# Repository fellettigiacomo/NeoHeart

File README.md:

# NeoHeart - Revision 2.2🎉
Hardware and Software design for an Open Source ATtiny816-based heart shaped PCB with Addressable LEDs.
<br><br>⚠️ **Warning**: Unfortunately, this release is not yet ready for production. There are still issues with the CR2032 battery not providing enough power, causing glitches and freezes in the LEDs. I'm currently working on a fix. ⚠️
<br><br>
## Project sponsor: PCBWay
Thanks to [PCBWay](https://www.pcbway.com/) for sponsoring this open-source project. Check out the sponsorship section below to learn more about their support.

## Features

- **Microcontroller**: ATtiny816
- **LEDs**: 25 SK6805-MINIJ Addressable RGB LEDs
- **Power**: 3V CR2032 battery
- **Programming**: UPDI programming interface
- **Software**: Built using Adafruit's Neopixel library, featuring 10 built-in animations and efficient power management
- **Additional Features**:
  - Low current consumption design
  - Integrated MOSFET for powering down LEDs to save power
  - Additional digital/analog exposed GPIO to hack your NeoHeart in unexpected ways
  
## 2.2 Upgrades

- **Efficient power design**: the TPS61240 boost converter has been fully redesigned—now controlled by the MCU via the Enable pin (no more external MOSFET). Improved input stability with additional capacitors, removed feedback resistors for better overall efficiency.
- **Extended Battery Life**: ultra-low 0.14 µA quiescent current enables over 10 years of idle operation and supports 1000+ button presses on a single CR2032 cell.
- **Enhanced ATiny816 Stability**: added decoupling capacitors to ensure reliable and noise-free microcontroller performance.
- **Upgraded Battery Holder**: replaced the CR2032 holder with a more robust and durable version to prevent mechanical failure.
- **Improved Grounding**: added a dedicated ground plane for better signal integrity and reduced noise.
    
## Getting Started

To get started with NeoHeart, follow these steps:
1. **Assembly**: 
   - If you didn't assemble the back using economic PCBA (which I recommend), solder the [battery holder](https://aliexpress.com/item/1005005506756152.html).
2. **Powering the Board**:
   - Insert a CR2032 battery into the battery holder, ensuring the positive side of the battery matches the positive marking on the board. Alternatively, you can also power the board with the 5V and GND headers
3. **Installing Software**:
   - Install the Legacy version of the [Arduino IDE](https://www.arduino.cc/en/software) (otherwise you will get the *a programmer is required to upload* error) or [PlatformIO](https://platformio.org/platformio-ide)
   - Install the Adafruit NeoPixel library.
4. **Connecting the Programmer**:
   - Connect your UPDI programmer to the UPDI header on your NeoHeart board. If using an Arduino or any other serial adapter that supports JTAG, follow the instructions provided [here](https://github.com/ElTangas/jtag2updi).
5. **Uploading the Firmware**:
   - Open the firmware sketch provided in the repository.
   - Select the correct board and port in your IDE of choice.
   - Click on the upload button to flash your NeoHeart.
6. **Enjoy**:
   - Once programmed, your NeoHeart will be ready to go. Just hit the button and watch those LEDs light up!

## Manufacturing
Without including taxes, shipping and with current parts pricing 5 assembled boards (front only, having to solder the battery holder yourself) will cost around 52 USD dollars, so around 10 bucks a board.
<br><br>You can find all the files for production in the *releases* tab of this repository.
<br>All parts should available and ready to order, otherwise, feel free to send me a pull request.

## Contributing
Any contribution aimed to improving the software or the hardware of NeoHeart are very welcomed. 
Please feel free to fork this repo, make changes, and submit pull requests.

## PCBWay
I've been able to prototype the latest NeoHeart Release thanks to PCBWay that reached out to sponsor this project.
<br> You can see a photo of the boards that PCBWay sent me down here, you can also watch my unboxing video [here](https://youtu.be/b7MC2HfKiS8)
### Why PCBWay?
- **Quality and Reliability**: PCBWay's PCBs meet the highest standards of quality and reliability, they are also capable of meeting the technical demands of any project, from simple projects like mine to very complicated projects.
- **Customization and Flexibility**: They offer extensive customization options, allowing board designers to tailor their PCBs precisely to their project's needs.
- **Community Support**: PCBWay is a strong supporter of open-source projects, offering sponsorships and discounts to help bring these community-beneficial projects to life. Their commitment to the open-source community makes them a particularly good match for community-driven initiatives.
- **Rapid Prototyping**: Time is very important in project development, and PCBWay’s rapid prototyping service allows for quick turnarounds without sacrificing quality.

### My Experience with PCBWay
It's been fantastic: our collaboration not only consisted in receiving high-quality PCBs (with PCBA), experiencing a seamless process facilitated by their expert team, from selecting the right components to checking for errors. 
<br>I've also received photos of the assembled boards before shipping to ensure everything was perfect!.
<br><br>Despite different time zones, the response time from their support team was impressive, which I found incredibly helpful.
<br><br>As I said before, I think it's fantastic that big companies like PCBWay are committed to the open-source community, helping students worldwide bring their projects to life. <b> Thanks again PCBWay!! </b>

## License
CERN Open Hardware License - Strongly Reciprocal (CERN-OHL-S)

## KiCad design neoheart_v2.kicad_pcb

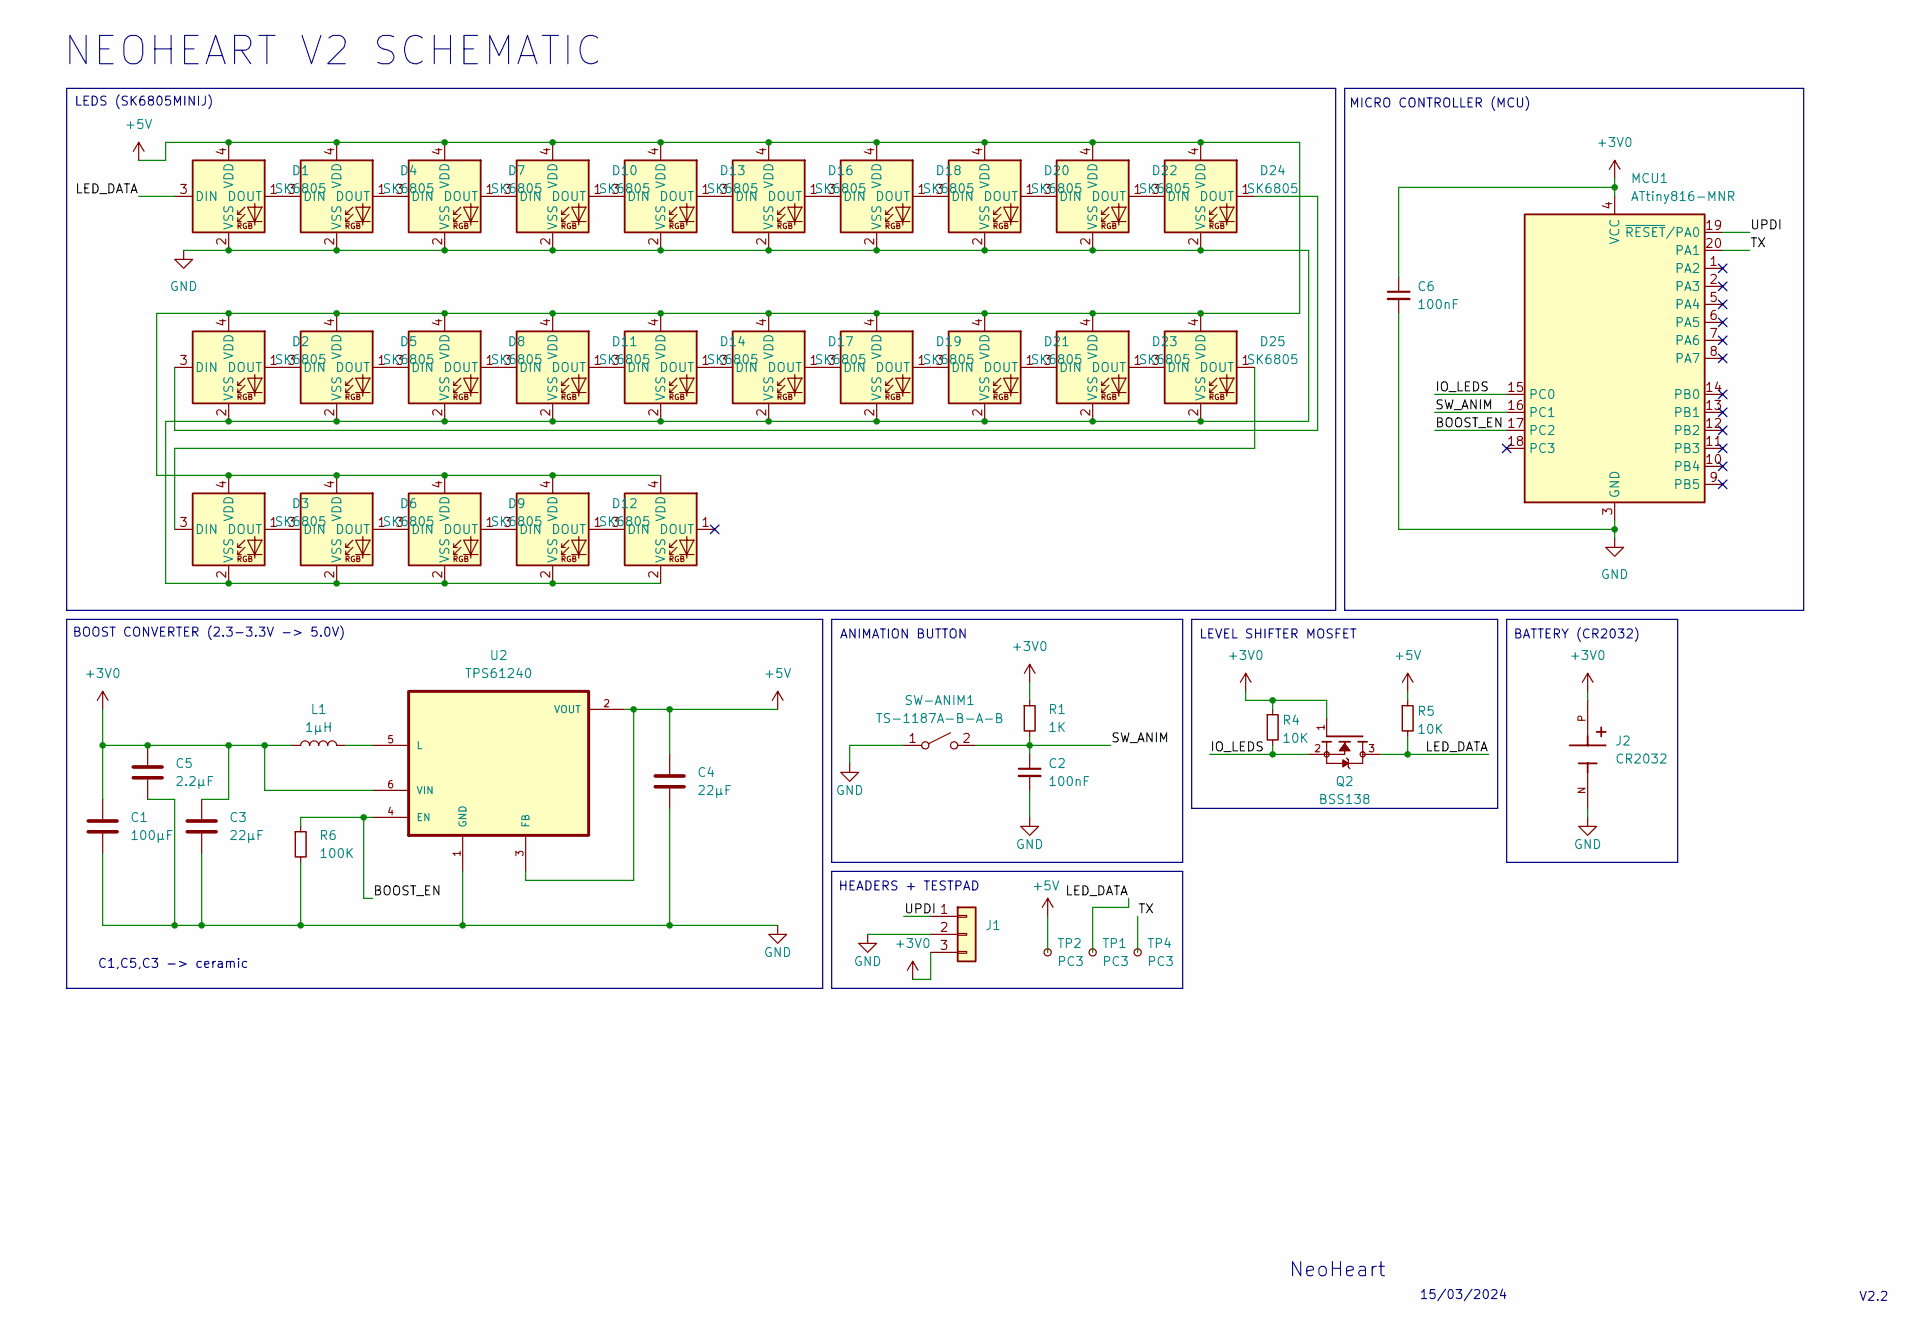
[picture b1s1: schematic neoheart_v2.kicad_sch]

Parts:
C1: 100µF; C_1210_3225Metric_Pad1.33x2.70mm_HandSolder
C2: 100nF; C_0402_1005Metric_Pad0.74x0.62mm_HandSolder
C3: 22μF; C_0805_2012Metric_Pad1.18x1.45mm_HandSolder
C4: 22μF; C_0603_1608Metric_Pad1.08x0.95mm_HandSolder
C5: 2.2µF; C_0805_2012Metric_Pad1.18x1.45mm_HandSolder
C6: 100nF; C_0603_1608Metric
D1, D2, D3, D4, D5, D6, D7, D8, D9, D10, D11, D12, D13, D14, D15, D16, D17, D18, D19, D20, D21, D22, D23, D24, D25: SK6805; LED_SK6805_PLCC4_2.4x2.7mm_P1.3mm
J1: Conn_01x03; PinHeader_1x03_P2.54mm_Vertical
J2: CR2032; HARWIN_S8421-45R; PARTREV 7
L1: 1μH; L_0805_2012Metric_Pad1.05x1.20mm_HandSolder
MCU1: ATtiny816-MNR; VQFN-20-1EP_3x3mm_P0.4mm_EP1.7x1.7mm
Q2: BSS138; SOT95P237X112-3N; PARTREV April 24, 2014
R1: 1K; R_0402_1005Metric_Pad0.72x0.64mm_HandSolder
R4, R5: 10K; R_0402_1005Metric_Pad0.72x0.64mm_HandSolder
R6: 100K; R_0805_2012Metric_Pad1.20x1.40mm_HandSolder
SW-ANIM1: TS-1187A-B-A-B; SW_Push_1P1T_XKB_TS-1187A
TP1, TP2, TP4: PC3; TestPoint_Pad_D1.5mm
U2: TPS61240; SON65P200X200X80-7N

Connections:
+3V0: C1.1, C3.1, C5.1, C6.1, J1.3, J2.P, L1.1, MCU1.4 (VCC), Q2.1, R1.1, R4.1, U2.6 (VIN)
+5V: C4.1, D1.4 (VDD), D2.4 (VDD), D3.4 (VDD), D4.4 (VDD), D5.4 (VDD), D6.4 (VDD), D7.4 (VDD), D8.4 (VDD), D9.4 (VDD), D10.4 (VDD), D11.4 (VDD), D12.4 (VDD), D13.4 (VDD), D14.4 (VDD), D15.4 (VDD), D16.4 (VDD), D17.4 (VDD), D18.4 (VDD), D19.4 (VDD), D20.4 (VDD), D21.4 (VDD), D22.4 (VDD), D23.4 (VDD), D24.4 (VDD), D25.4 (VDD), R5.1, TP2.1, U2.2 (VOUT), U2.3 (FB)
/BOOST_EN: MCU1.17 (PC2), R6.1, U2.4 (EN)
/IO_LEDS: MCU1.15 (PC0), Q2.2, R4.2
/LED_DATA: D1.3 (DIN), Q2.3, R5.2, TP1.1
/SW_ANIM: C2.1, MCU1.16 (PC1), R1.2, SW-ANIM1.2 (B)
/TX: MCU1.20 (PA1), TP4.1
/UPDI: J1.1, MCU1.19 (~RESET/PA0)
GND: C1.2, C2.2, C3.2, C4.2, C5.2, C6.2, D1.2 (VSS), D2.2 (VSS), D3.2 (VSS), D4.2 (VSS), D5.2 (VSS), D6.2 (VSS), D7.2 (VSS), D8.2 (VSS), D9.2 (VSS), D10.2 (VSS), D11.2 (VSS), D12.2 (VSS), D13.2 (VSS), D14.2 (VSS), D15.2 (VSS), D16.2 (VSS), D17.2 (VSS), D18.2 (VSS), D19.2 (VSS), D20.2 (VSS), D21.2 (VSS), D22.2 (VSS), D23.2 (VSS), D24.2 (VSS), D25.2 (VSS), J1.2, J2.N, MCU1.3 (GND), MCU1.21 (GND), R6.2, SW-ANIM1.1 (A), U2.1 (GND)
unnamed: D1.1 (DOUT), D4.3 (DIN)
unnamed: D2.3 (DIN), D24.1 (DOUT)
unnamed: D2.1 (DOUT), D5.3 (DIN)
unnamed: D3.1 (DOUT), D6.3 (DIN)
unnamed: D4.1 (DOUT), D7.3 (DIN)
unnamed: D5.1 (DOUT), D8.3 (DIN)
unnamed: D6.1 (DOUT), D9.3 (DIN)
unnamed: D7.1 (DOUT), D10.3 (DIN)
unnamed: D10.1 (DOUT), D13.3 (DIN)
unnamed: D8.1 (DOUT), D11.3 (DIN)
unnamed: D11.1 (DOUT), D14.3 (DIN)
unnamed: D9.1 (DOUT), D12.3 (DIN)
unnamed: D12.1 (DOUT), D15.3 (DIN)
unnamed: D13.1 (DOUT), D16.3 (DIN)
unnamed: D14.1 (DOUT), D17.3 (DIN)
unnamed: D16.1 (DOUT), D18.3 (DIN)
unnamed: D17.1 (DOUT), D19.3 (DIN)
unnamed: D18.1 (DOUT), D20.3 (DIN)
unnamed: D19.1 (DOUT), D21.3 (DIN)
unnamed: D20.1 (DOUT), D22.3 (DIN)
unnamed: D21.1 (DOUT), D23.3 (DIN)
unnamed: D22.1 (DOUT), D24.3 (DIN)
unnamed: D23.1 (DOUT), D25.3 (DIN)
unnamed: D3.3 (DIN), D25.1 (DOUT)
unnamed: L1.2, U2.5 (L)

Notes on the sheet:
MICRO CONTROLLER (MCU)
NEOHEART V2 SCHEMATIC
BATTERY (CR2032)
C1,C5,C3 -> ceramic
NeoHeart
HEADERS + TESTPAD
ANIMATION BUTTON
BOOST CONVERTER (2.3-3.3V -> 5.0V)
15/03/2024
LEDS (SK6805MINIJ)
V2.2
LEVEL SHIFTER MOSFET

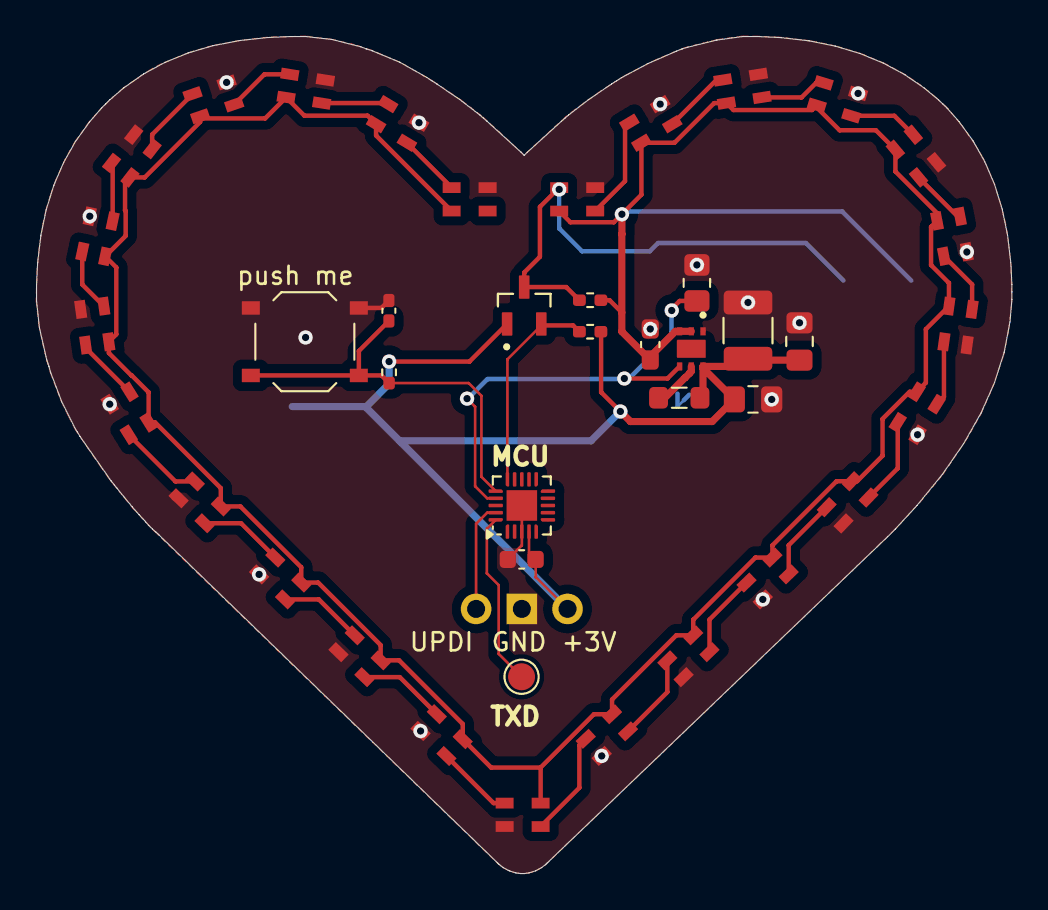
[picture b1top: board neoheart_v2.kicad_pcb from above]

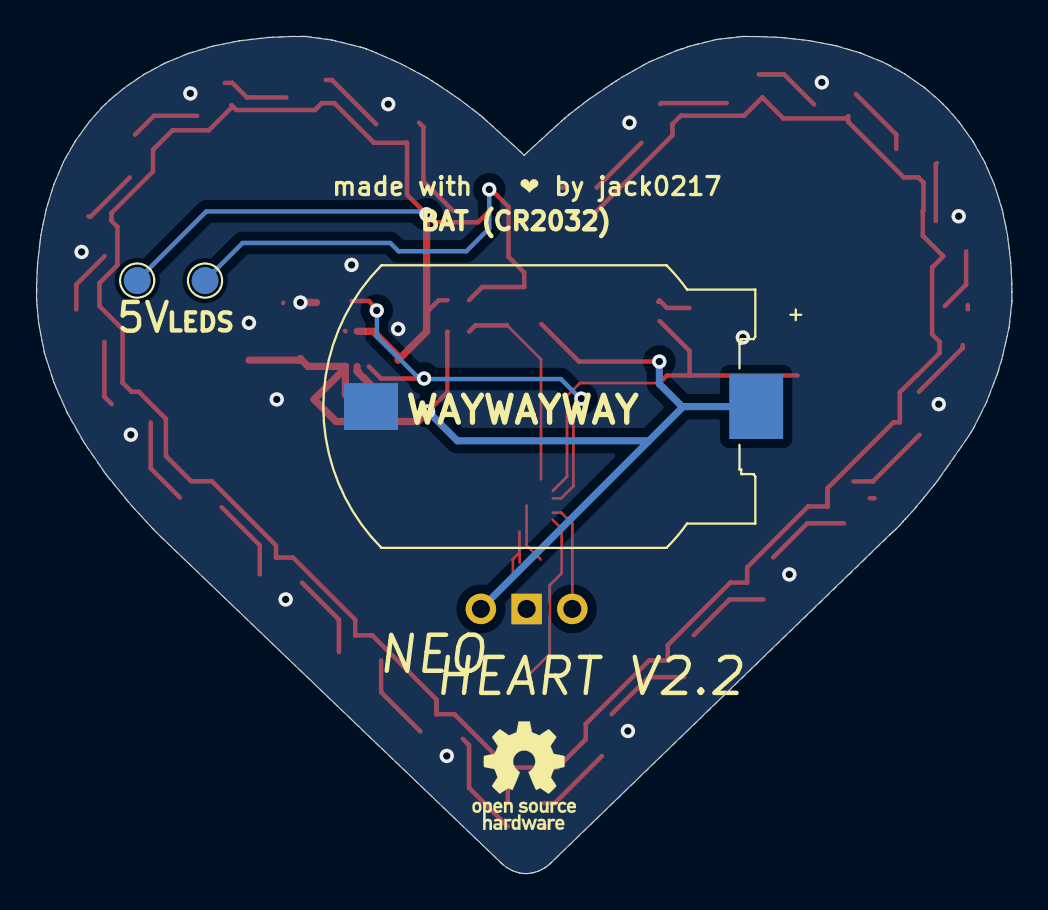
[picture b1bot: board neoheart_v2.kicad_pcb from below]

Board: 2 copper layers, 54.2 x 46.5 mm, 45 parts (3 on the bottom side), 34 nets.

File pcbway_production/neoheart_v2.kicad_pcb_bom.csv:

designator,quantity,value,pack,mpn,mount_type
BT1,1,Battery,BatteryHolder_Keystone_1060_1x2032,,smt
C2,1,100nF,C_0402_1005Metric_Pad0.74x0.62mm_HandSolder,,smt
"C3, C4",2,22μF,C_0603_1608Metric,,smt
"D1, D10, D11, D12, D13, D14, D15, D16, D17, D18, D19, D2, D20, D21, D22, D23, D24, D25, D3, D4, D5, D6, D7, D8, D9",25,SK6805,LED_SK6805_PLCC4_2.4x2.7mm_P1.3mm,,smt
J1,1,Conn_01x03,PinHeader_1x03_P2.54mm_Vertical,,tht
L1,1,MLP2012V4R7MT0S1,L_0805_2012Metric,,smt
MCU1,1,ATtiny816-MNR,VQFN-20-1EP_3x3mm_P0.4mm_EP1.7x1.7mm,,smt
Q1,1,A1SHB,SOT95P237X112-3N,,smt
Q2,1,BSS138,SOT95P237X112-3N,,smt
R1,1,1K,R_0402_1005Metric_Pad0.72x0.64mm_HandSolder,,smt
R2,1,180kΩ,R_0805_2012Metric,,smt
R3,1,"1,5MΩ",R_0603_1608Metric,,smt
"R4, R5",2,10K,R_0402_1005Metric_Pad0.72x0.64mm_HandSolder,,smt
SW-ANIM1,1,TS-1187A-B-A-B,SW_Push_1P1T_XKB_TS-1187A,,smt
"TP1, TP2, TP4",3,PC3,TestPoint_Pad_D1.0mm,,tht
U2,1,TPS61240TDRVRQ1,SON65P200X200X80-7N,,smt

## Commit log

2024-05-06 uploaded hardware
    uploaded final version of the board with production files and library for 3D models, footprints and symbols.
2024-05-06 uploaded firmware
2024-05-06 added license file
2024-05-08 deleted neoheart_v2.kicad_prl
2024-05-08 updated schematic
2024-05-08 uploaded hardware
2024-05-08 updated neoheart_v2.kicad_sch
2024-05-28 moved to platformio
2024-05-28 updated firmware: mosfet, sleep, bugfixes
2024-05-28 lowered brightness for boost converter stability
2024-05-28 added board render, cleanup, new production files
2024-05-28 added image url
2024-05-28 updated .gitignore
2024-05-28 Optimize NeoPixel library
    And add support for running at 8MHz
2024-05-29 Fix glitches by disabling/enabling interrupts
2024-05-29 Remove support for 400MHz NeoPixels
    We don't need them
2024-05-29 Optimize clearing the strip
2024-05-31 unfinished - revision 2.1
2024-05-31 fixed @depau's battery orientation trigger
2024-06-02 board revision 2.1
2024-06-02 updated silkscreen text
2024-06-04 revision 2.1, pcbway production files
2024-06-11 add 3d models, new board render
2024-07-10 add pcbway's board image
2024-07-11 update readme, pcbway sponsorship
2025-03-25 2.2: update schematic, new boost converter design, hardware optimizations
2025-03-30 2.2: update PCB, add production files, new board renders
2025-05-11 change level shifter mosfet
2025-05-11 2.2 firmware: code refactor
